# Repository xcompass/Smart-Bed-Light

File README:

SmartBedLight

An automated smart bed night light with ATMega328 and TLC5940.
For configuration, please refer to http://code.google.com/p/tlc5940arduino/

Version 1 and 2 are using TLC5940. Version 3 is using 74595 shifter chip.

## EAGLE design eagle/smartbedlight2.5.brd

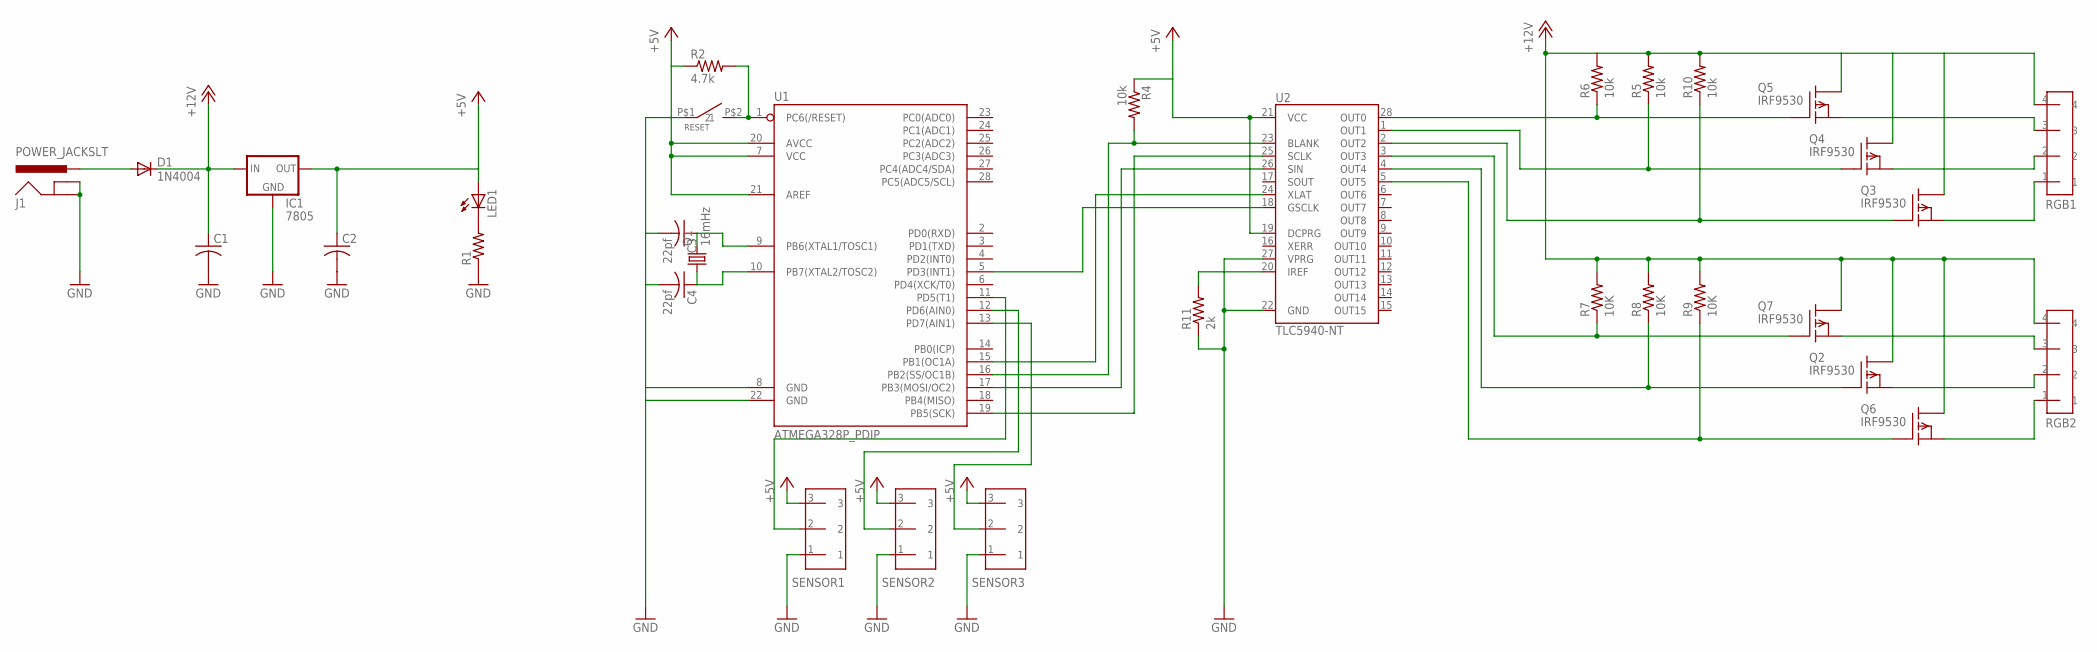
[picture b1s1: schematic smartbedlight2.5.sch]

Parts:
C1, C2: C-US025-030X050; C025-030X050
C3, C4: 22pf; C025-025X050
D1: 1N4004; DO41-10
IC1: 7805; 78XXL
J1: POWER_JACKSLT; POWER_JACK_SLOT
LED1: LED5MM
Q1: 16mHz; HC49U-V
Q2, Q3, Q4, Q5, Q6, Q7: IRF9530; TO220
R1: R-US_0204/7; 0204/7
R2: 4.7k; 0207/10
R4: 10k; 0207/10
R5, R6, R10: 10k; M0805
R7, R8, R9: 10K; M0805
R11: 2k; 0207/10
RESET: TACK_SWITCH
RGB1, RGB2: PINHEAD4
SENSOR1, SENSOR2, SENSOR3: PINHEAD3; PINHEAD
U1: ATMEGA328P_PDIP; DIL28-3
U2: TLC5940-NT; DIL28-3

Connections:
+5V: C2.1, IC1.OUT, LED1.A, R2.1, R4.1, SENSOR1.3, SENSOR2.3, SENSOR3.3, U1.7 (VCC), U1.20 (AVCC), U1.21 (AREF), U2.19 (DCPRG), U2.21 (VCC)
+12V: C1.1, D1.C, IC1.IN, Q2.2 (D), Q3.2 (D), Q4.2 (D), Q5.2 (D), Q6.2 (D), Q7.2 (D), R5.2, R6.2, R7.2, R8.2, R9.2, R10.2, RGB1.4, RGB2.4
GND: C1.2, C2.2, C3.2, C4.2, IC1.GND, J1.GND@1 (GNDBREAK), J1.GND@2 (GND), R1.1, R11.1, RESET.P$1 (1), SENSOR1.1, SENSOR2.1, SENSOR3.1, U1.8 (GND), U1.22 (GND), U2.22 (GND), U2.27 (VPRG)
unnamed: LED1.K (C), R1.2
unnamed: D1.A, J1.PWR
unnamed: R2.2, RESET.P$2 (2), U1.1 (PC6(/RESET))
unnamed: R4.2, U1.16 (PB2(SS/OC1B)), U2.23 (BLANK)
unnamed: C4.1, Q1.1, U1.10 (PB7(XTAL2/TOSC2))
unnamed: SENSOR2.2, U1.12 (PD6(AIN0))
unnamed: U1.5 (PD3(INT1)), U2.18 (GSCLK)
unnamed: SENSOR1.2, U1.11 (PD5(T1))
unnamed: SENSOR3.2, U1.13 (PD7(AIN1))
unnamed: Q3.1 (G), R10.1, U2.2 (OUT2)
unnamed: U1.17 (PB3(MOSI/OC2)), U2.26 (SIN)
unnamed: Q7.1 (G), R7.1, U2.3 (OUT3)
unnamed: Q6.1 (G), R9.1, U2.5 (OUT5)
unnamed: Q2.1 (G), R8.1, U2.4 (OUT4)
unnamed: Q5.1 (G), R6.1, U2.28 (OUT0)
unnamed: Q4.1 (G), R5.1, U2.1 (OUT1)
unnamed: U1.19 (PB5(SCK)), U2.25 (SCLK)
unnamed: U1.15 (PB1(OC1A)), U2.24 (XLAT)
unnamed: Q6.3 (S), RGB2.1
unnamed: Q2.3 (S), RGB2.2
unnamed: Q7.3 (S), RGB2.3
unnamed: Q5.3 (S), RGB1.3
unnamed: Q4.3 (S), RGB1.2
unnamed: Q3.3 (S), RGB1.1
unnamed: R11.2, U2.20 (IREF)
unnamed: C3.1, Q1.2, U1.9 (PB6(XTAL1/TOSC1))

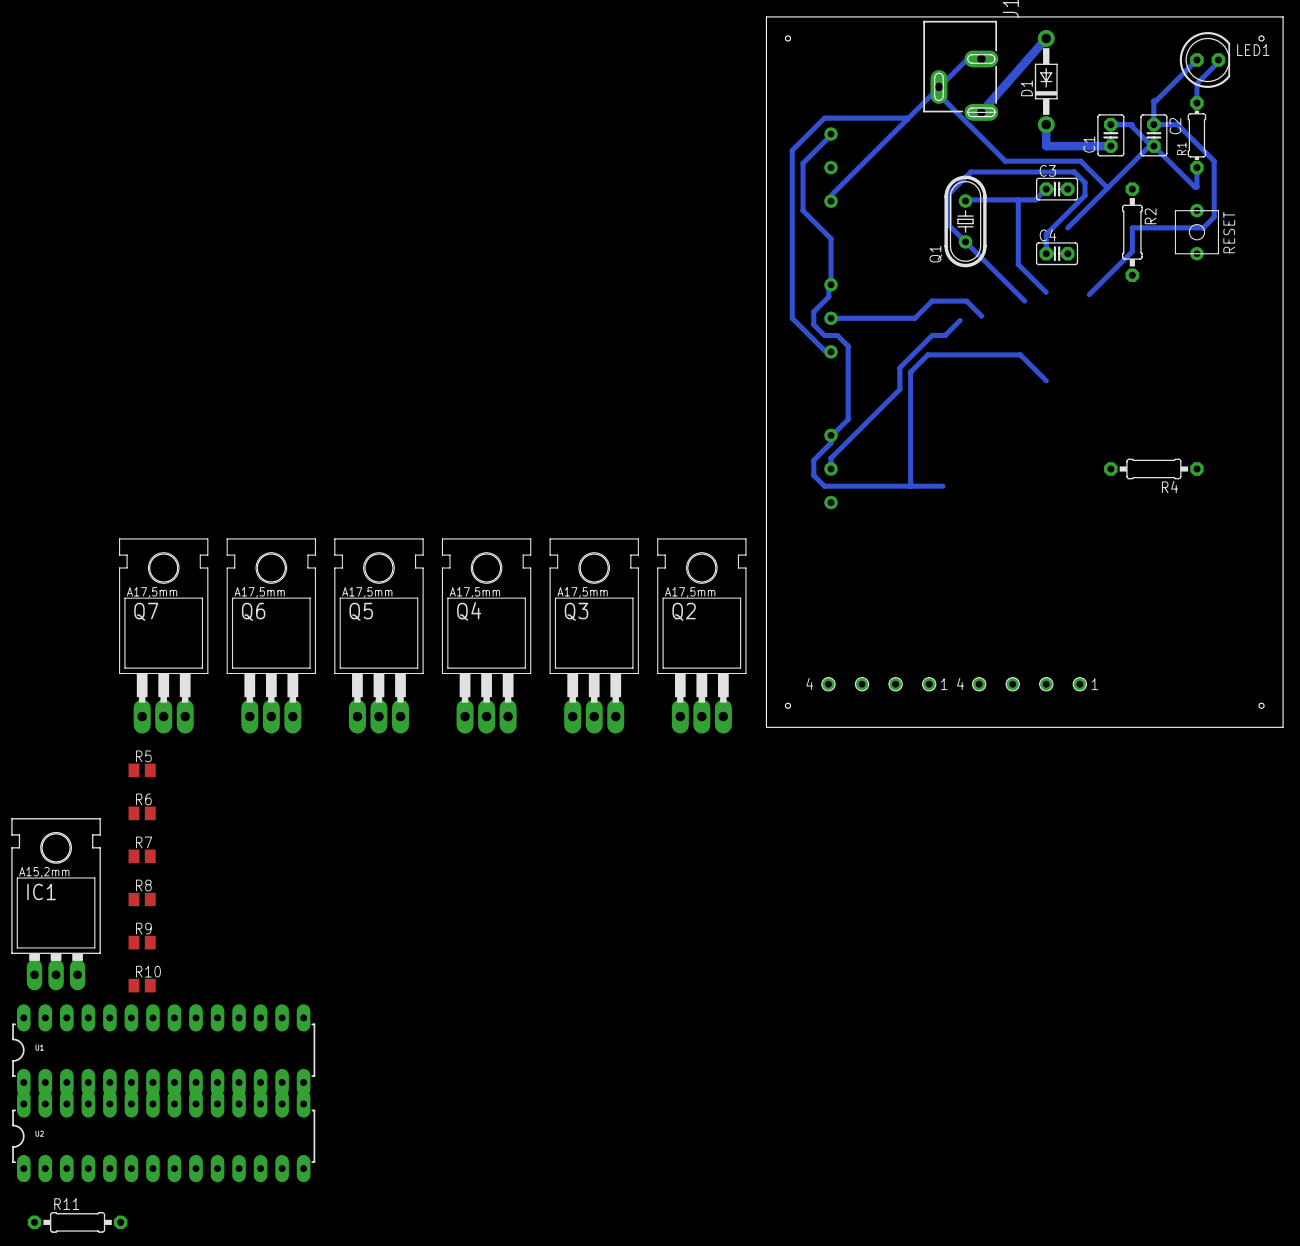
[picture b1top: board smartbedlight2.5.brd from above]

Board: 2 copper layers, 61.0 x 83.8 mm, 33 parts (0 on the bottom side), 29 nets.

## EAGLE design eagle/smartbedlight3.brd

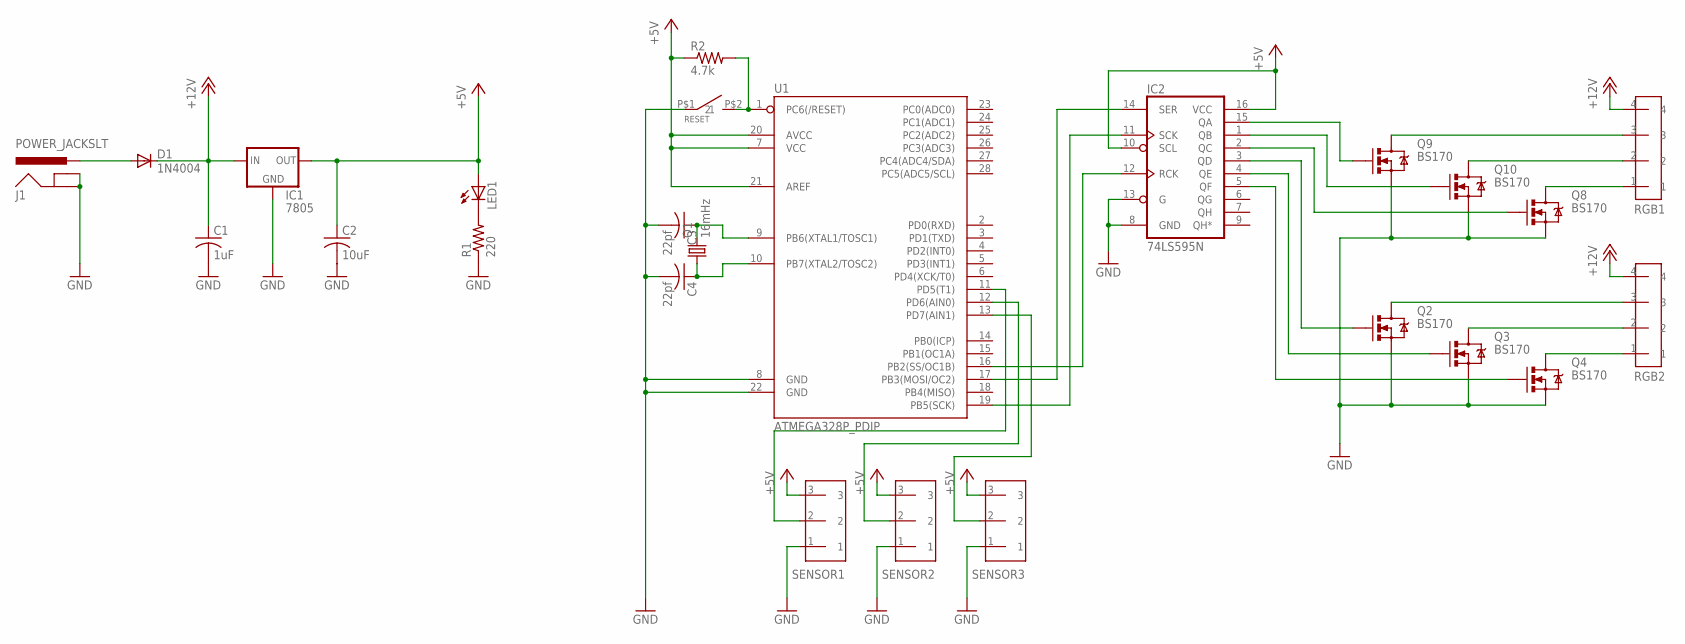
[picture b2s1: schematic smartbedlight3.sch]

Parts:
C1: 1uF; C025-030X050
C2: 10uF; C025-030X050
C3, C4: 22pf; C025-025X050
D1: 1N4004; DO41-10
IC1: 7805; 78XXL
IC2: 74LS595N; DIL16
J1: POWER_JACKSLT; POWER_JACK_SLOT
LED1: LED5MM
Q1: 16mHz; HC49U-V
Q2, Q3, Q4, Q8, Q9, Q10: BS170; TO-92
R1: 220; 0204/7
R2: 4.7k; 0207/10
RESET: TACK_SWITCH
RGB1, RGB2: PINHEAD4
SENSOR1, SENSOR2, SENSOR3: PINHEAD3; PINHEAD
U1: ATMEGA328P_PDIP; DIL28-3

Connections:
+5V: C2.1, IC1.OUT, IC2.10 (SCL), IC2.16 (VCC), LED1.A, R2.1, SENSOR1.3, SENSOR2.3, SENSOR3.3, U1.7 (VCC), U1.20 (AVCC), U1.21 (AREF)
+12V: C1.1, D1.C, IC1.IN, RGB1.4, RGB2.4
GND: C1.2, C2.2, C3.2, C4.2, IC1.GND, IC2.8 (GND), IC2.13 (G), J1.GND@1 (GNDBREAK), J1.GND@2 (GND), Q2.3 (S), Q3.3 (S), Q4.3 (S), Q8.3 (S), Q9.3 (S), Q10.3 (S), R1.1, RESET.P$1 (1), SENSOR1.1, SENSOR2.1, SENSOR3.1, U1.8 (GND), U1.22 (GND)
unnamed: LED1.K (C), R1.2
unnamed: D1.A, J1.PWR
unnamed: R2.2, RESET.P$2 (2), U1.1 (PC6(/RESET))
unnamed: IC2.15 (QA), Q9.2 (G)
unnamed: C4.1, Q1.1, U1.10 (PB7(XTAL2/TOSC2))
unnamed: IC2.12 (RCK), U1.16 (PB2(SS/OC1B))
unnamed: SENSOR2.2, U1.12 (PD6(AIN0))
unnamed: Q9.1 (D), RGB1.3
unnamed: SENSOR1.2, U1.11 (PD5(T1))
unnamed: SENSOR3.2, U1.13 (PD7(AIN1))
unnamed: IC2.2 (QC), Q8.2 (G)
unnamed: IC2.14 (SER), U1.17 (PB3(MOSI/OC2))
unnamed: IC2.3 (QD), Q2.2 (G)
unnamed: IC2.5 (QF), Q4.2 (G)
unnamed: IC2.4 (QE), Q3.2 (G)
unnamed: Q10.1 (D), RGB1.2
unnamed: IC2.1 (QB), Q10.2 (G)
unnamed: IC2.11 (SCK), U1.19 (PB5(SCK))
unnamed: Q8.1 (D), RGB1.1
unnamed: Q4.1 (D), RGB2.1
unnamed: Q2.1 (D), RGB2.3
unnamed: Q3.1 (D), RGB2.2
unnamed: C3.1, Q1.2, U1.9 (PB6(XTAL1/TOSC1))

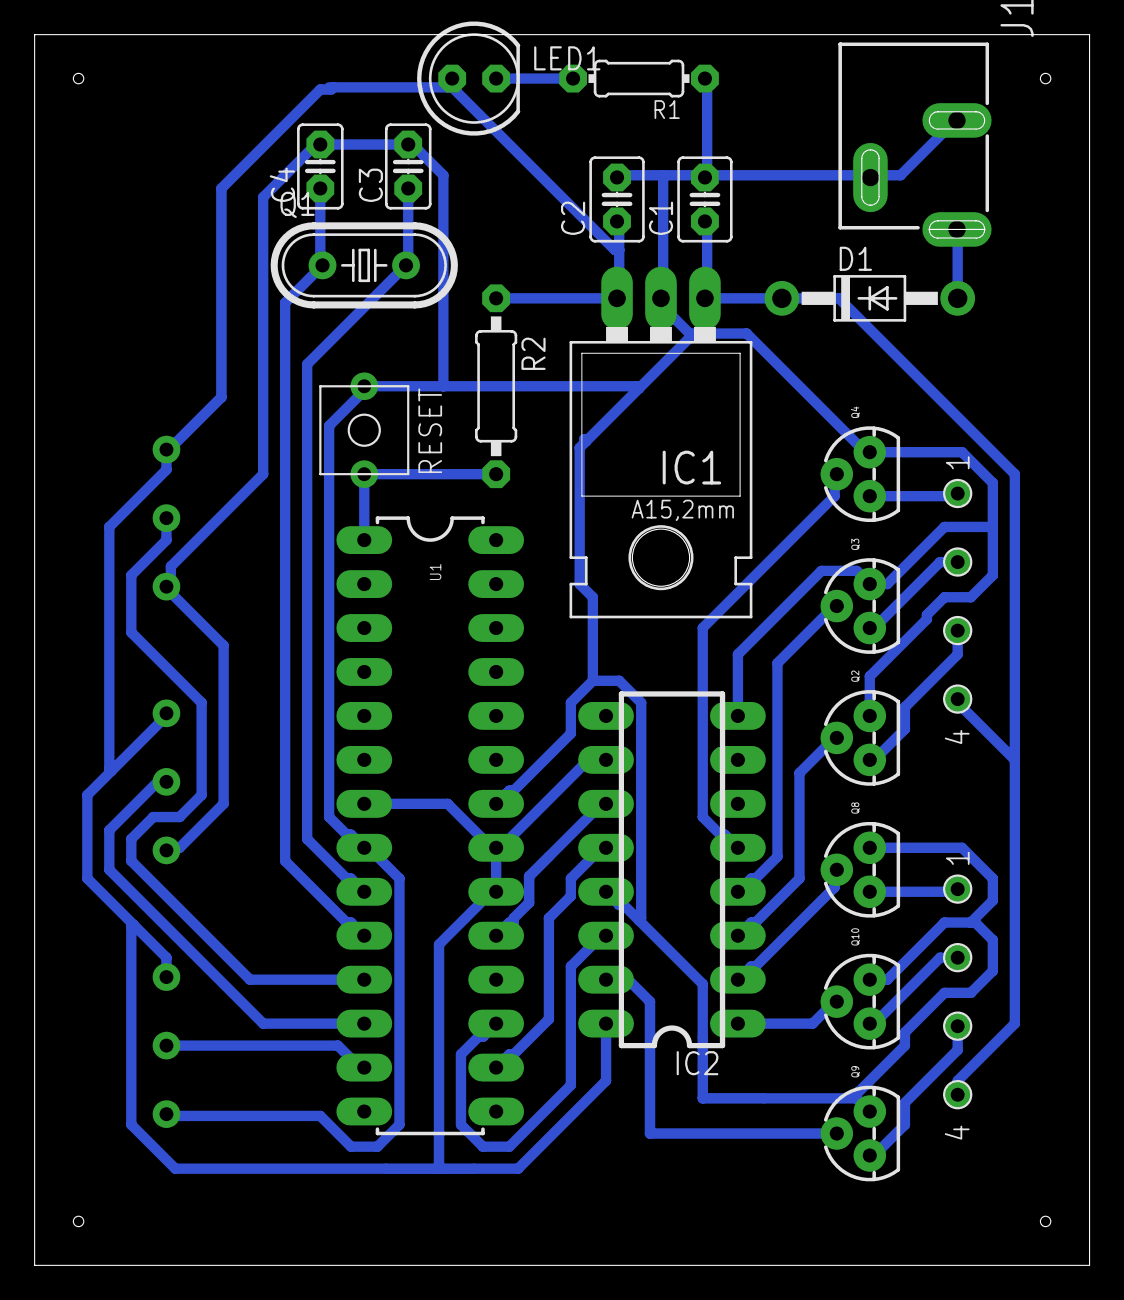
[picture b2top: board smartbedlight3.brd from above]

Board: 2 copper layers, 61.0 x 71.1 mm, 25 parts (0 on the bottom side), 26 nets.

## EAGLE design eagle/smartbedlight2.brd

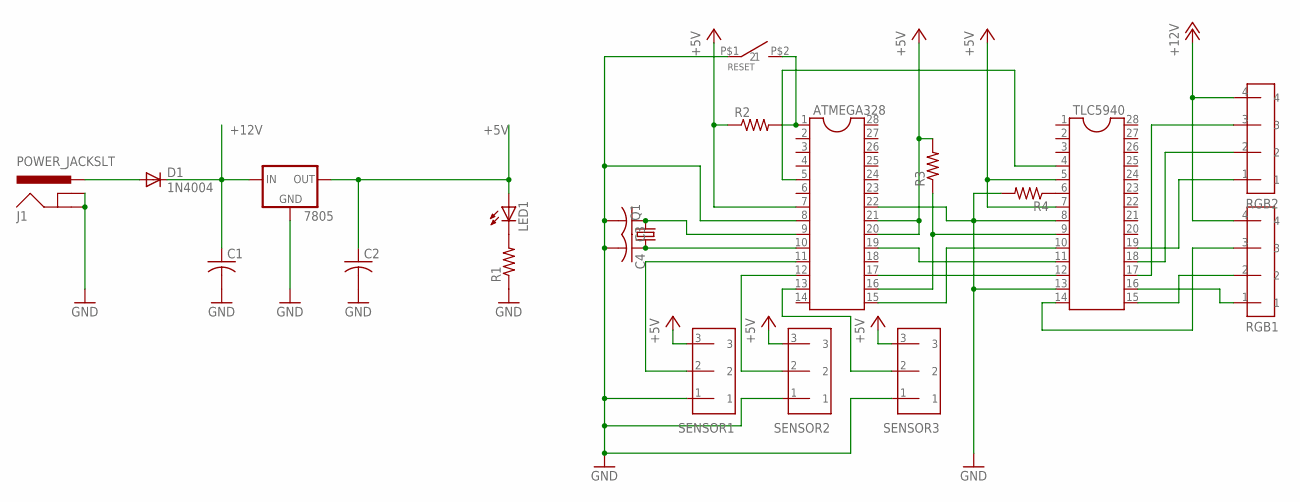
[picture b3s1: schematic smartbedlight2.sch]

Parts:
7805: V_REG_78XXSIDE; 78XXL
ATMEGA328: DIL28-3
C1, C2: C-US025-030X050; C025-030X050
C3, C4: C-US025-025X050; C025-025X050
D1: 1N4004; DO41-10
J1: POWER_JACKSLT; POWER_JACK_SLOT
LED1: LED5MM
Q1: CRYSTALHC49U-V; HC49U-V
R1: R-US_0204/7; 0204/7
R2, R3, R4: R-US_0207/10; 0207/10
RESET: TACK_SWITCH
RGB1, RGB2: PINHEAD4
SENSOR1, SENSOR2, SENSOR3: PINHEAD3; PINHEAD
TLC5940: DIL28-3

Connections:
+5V: 7805.OUT, ATMEGA328.7, ATMEGA328.20, ATMEGA328.21, C2.1, LED1.A, R2.1, R3.2, SENSOR1.3, SENSOR2.3, SENSOR3.3, TLC5940.5, TLC5940.7
+12V: 7805.IN, C1.1, D1.C, RGB1.4, RGB2.4
GND: 7805.GND, ATMEGA328.8, ATMEGA328.22, C1.2, C2.2, C3.2, C4.2, J1.GND@1 (GNDBREAK), J1.GND@2 (GND), R1.1, R4.2, RESET.P$1 (1), SENSOR1.1, SENSOR2.1, SENSOR3.1, TLC5940.8, TLC5940.13
unnamed: LED1.K (C), R1.2
unnamed: D1.A, J1.PWR
unnamed: ATMEGA328.1, R2.2, RESET.P$2 (2)
unnamed: ATMEGA328.9, C3.1, Q1.2
unnamed: ATMEGA328.10, C4.1, Q1.1
unnamed: ATMEGA328.19, TLC5940.11
unnamed: ATMEGA328.17, TLC5940.12
unnamed: ATMEGA328.16, R3.1, TLC5940.9
unnamed: ATMEGA328.15, TLC5940.10
unnamed: R4.1, TLC5940.6
unnamed: RGB2.1, TLC5940.19
unnamed: ATMEGA328.5, TLC5940.4
unnamed: RGB1.3, TLC5940.14
unnamed: RGB1.2, TLC5940.15
unnamed: RGB1.1, TLC5940.16
unnamed: RGB2.3, TLC5940.17
unnamed: RGB2.2, TLC5940.18
unnamed: ATMEGA328.11, SENSOR1.2
unnamed: ATMEGA328.12, SENSOR2.2
unnamed: ATMEGA328.13, SENSOR3.2

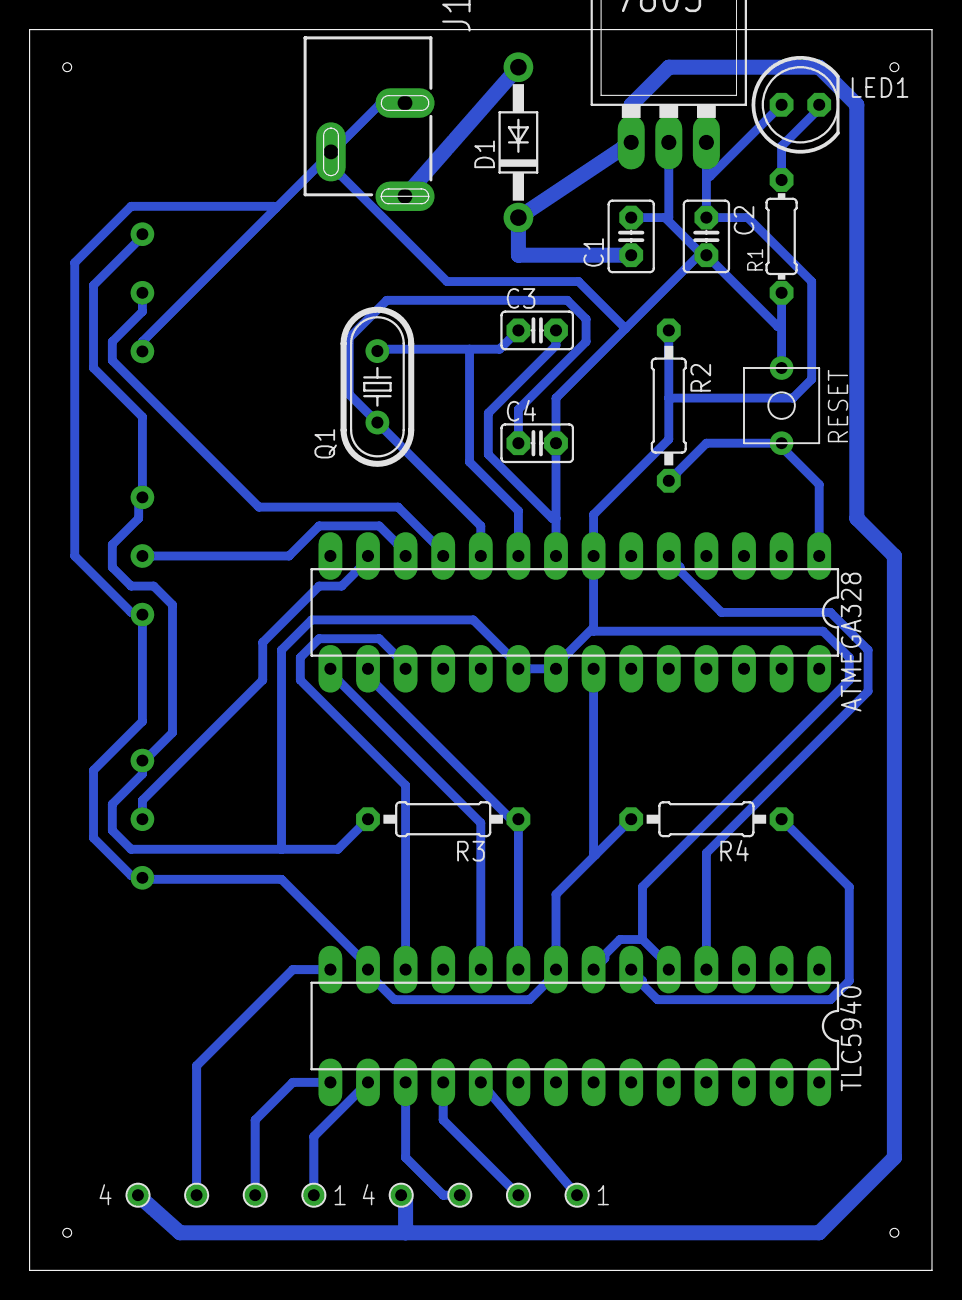
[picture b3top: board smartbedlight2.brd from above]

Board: 2 copper layers, 61.0 x 83.8 mm, 21 parts (0 on the bottom side), 23 nets.

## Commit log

2012-01-25 first commit, verison 1 and untested version 2
2012-01-25 Added link for hardware configuration
2012-01-30 moved ino file into directories. Fixed bug in V2 and tested V2.
2013-08-17 Add schema and board eagle files
2016-10-18 Add version 3

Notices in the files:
parts and their libraries:
SparkFun: Licensing: CC v3.0 Share-Alike You are welcome to use this library for commercial purposes.
